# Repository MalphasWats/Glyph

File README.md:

# Glyph

![Glyph][GLYPH]

Glyph is a handheld gaming device based on the ATMega1284P micro controller.

This repository contains the mechanical components - KiCAD PCB & laser cut case.

## Specification

* ATMega1284P @ 16MHz. 128kB Flash, 16kB SRAM
* 1.3" monochrome OLED display
* 8 soft buttons
* 2 channel sound via piezo speaker
* 2 programmable red LEDs

## PCB

[KiCAD symbol/footprint library][KiLIB]

## Code

A software library for controlling the hardware and building simple games is available here:

[glyphlib][GLYPHLIB]

## Games

* [Argon][ARGON]
* ... more soon

[GLYPH]: resources/glyph.jpeg
[GLYPHLIB]: https://github.com/MalphasWats/glyphlib
[ARGON]: https://github.com/MalphasWats/Argon
[KiLIB]: https://github.com/MalphasWats/KiCADLib

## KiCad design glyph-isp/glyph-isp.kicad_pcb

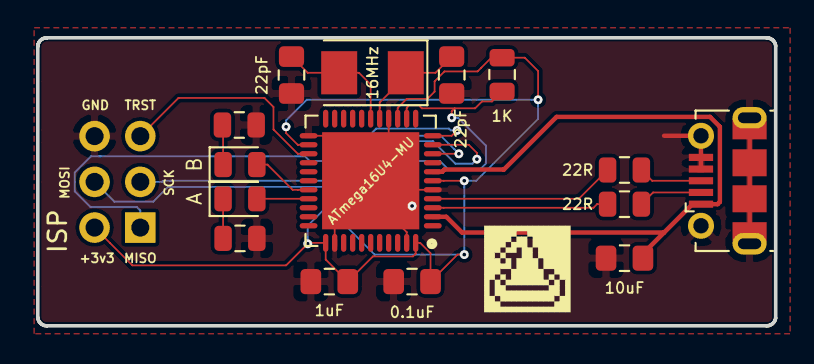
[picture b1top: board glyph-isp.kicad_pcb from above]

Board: 2 copper layers, 41.0 x 16.0 mm, 18 parts (1 on the bottom side), 18 nets.

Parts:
C0: 0.1uF; C_0805_2012Metric_Pad1.15x1.40mm_HandSolder
C1, C2: 22pF; C_0805_2012Metric_Pad1.15x1.40mm_HandSolder
C3: 1uF; C_0805_2012Metric_Pad1.15x1.40mm_HandSolder
C4: 10uF; C_0805_2012Metric_Pad1.15x1.40mm_HandSolder
D1: LED1; LED_0805_2012Metric
D2: LED2; LED_0805_2012Metric
HAT: HAT
J0, J1: ISP; PinHeader_2x03_P2.54mm_Vertical
J2: USB-Micro; USB_Micro-B_Molex-105017-0001
R1: 1K; R_0805_2012Metric
R2, R3: LED; R_0805_2012Metric
R4, R5: 22R; R_0805_2012Metric
U0: ATmega16U4-MU; QFN-44-1EP_7x7mm_P0.5mm_EP5.4x5.4mm
Y1: 16MHz; Crystal_SMD_5032-2Pin_5.0x3.2mm

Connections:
+3V3: C0.1, C3.1, J0.2, J1.2, R1.1, U0.6, U0.14, U0.24, U0.34, U0.44
D+: R4.1, U0.4
D-: R5.1, U0.3
GND: C0.2, C1.2, C2.2, C3.2, C4.1, J0.6, J1.6, J2.4, J2.5, J2.6, R2.2, R3.2, U0.5, U0.15, U0.23, U0.35, U0.43, U0.45
LED1: D1.2, U0.29
LED2: D2.2, U0.30
MISO: J0.1, J1.1, U0.11
MOSI: J0.4, J1.4, U0.10
unnamed: C1.1, U0.17, Y1.2
unnamed: C2.1, U0.16, Y1.1
unnamed: D1.1, R2.1
unnamed: D2.1, R3.1
unnamed: J2.2, R5.2
unnamed: J2.3, R4.2
RESET: J0.5, R1.2, U0.13
SCK: J0.3, J1.3, U0.9
TARGET_RESET: J1.5, U0.25
VBUS: C4.2, J2.1, U0.2, U0.7

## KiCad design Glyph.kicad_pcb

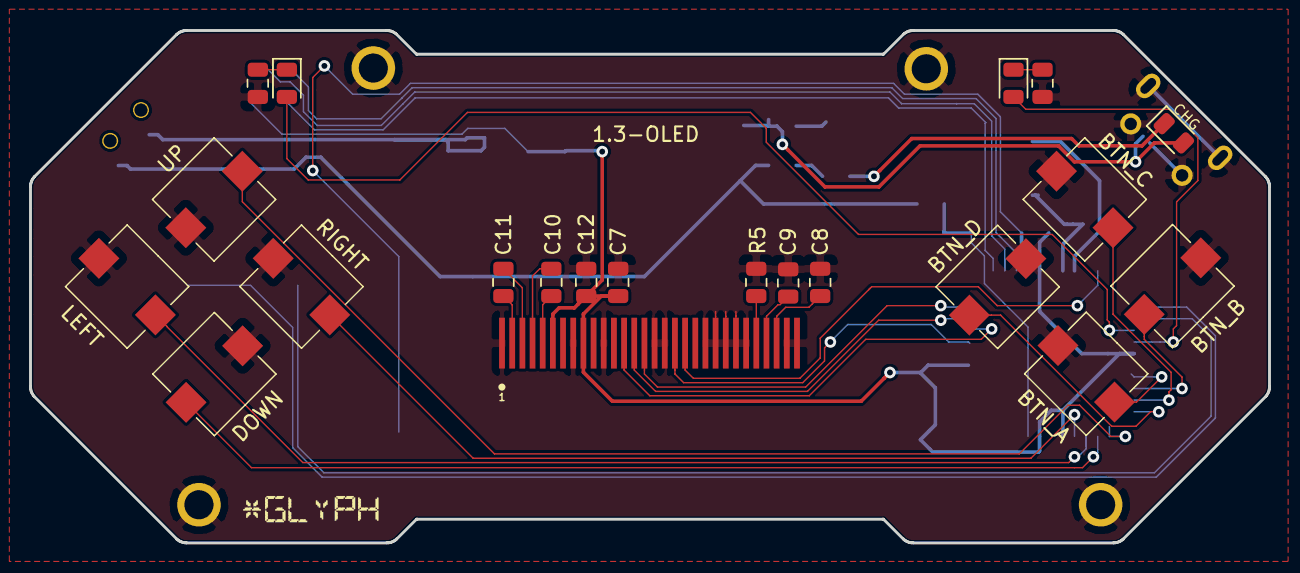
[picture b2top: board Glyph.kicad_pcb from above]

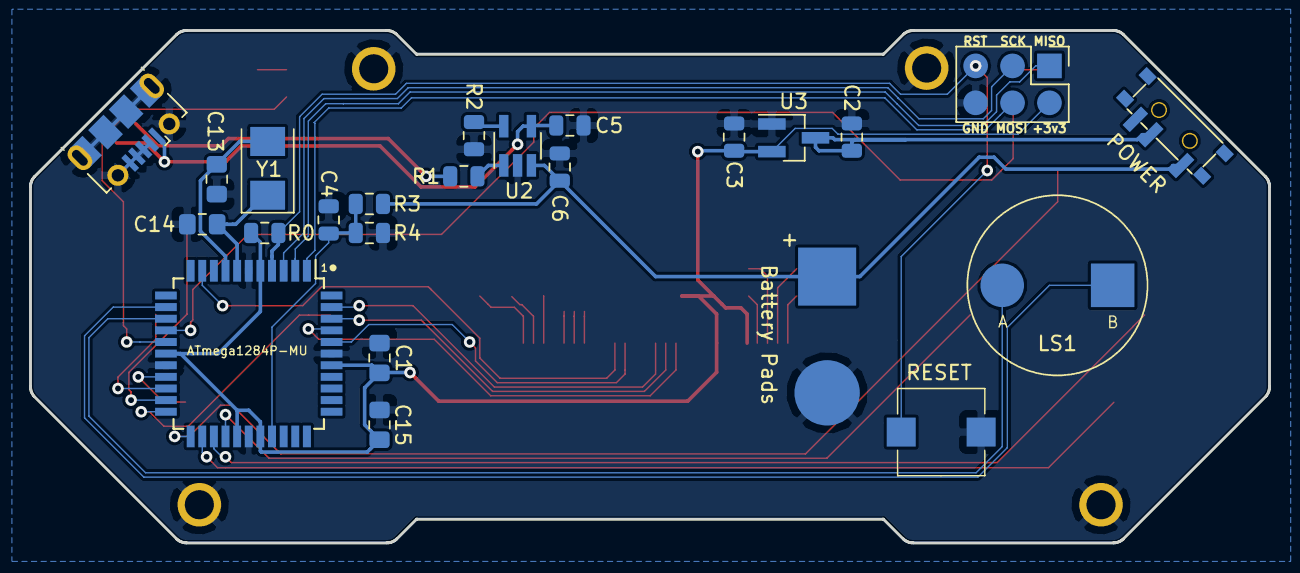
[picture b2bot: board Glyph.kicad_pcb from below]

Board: 2 copper layers, 85.3 x 35.3 mm, 50 parts (24 on the bottom side), 41 nets.

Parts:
C1, C15: 0.1uF; C_0805_2012Metric_Pad1.15x1.40mm_HandSolder
C2, C3, C4, C10, C11: 1uF; C_0805_2012Metric
C5, C6: 4.7uF; C_0805_2012Metric
C7, C12: 0.1uF; C_0805_2012Metric
C8: 47uF; C_0805_2012Metric
C9: 22uF; C_0805_2012Metric
C13, C14: 22pF; C_0805_2012Metric_Pad1.15x1.40mm_HandSolder
D0: CHG; LED_0805_2012Metric
D1: USR_1; LED_0805_2012Metric
D2: USR_2; LED_0805_2012Metric
J0: Battery Pads; 150mAh-Lipo
J1: ISP; ISP_SMD
J2: USB-Micro; USB_Micro-B_Molex-105017-0001
J3: Screw Point 1; M2_SCREW_HOLE
J4: Screw Point 2; M2_SCREW_HOLE
J5: Screw Point 3; M2_SCREW_HOLE
J6: Screw Point 4; M2_SCREW_HOLE
LOGO: LOGO
LS1: Speaker; Generic_Speaker
R0: 1K; R_0805_2012Metric
R1, R6, R7: LED; R_0805_2012Metric
R2: 2K; R_0805_2012Metric
R3, R4: 10M; R_0805_2012Metric
R5: 290k; R_0805_2012Metric
SW0: RESET; SW_SOFT_SMD_6mm
SW1: UP; SW_SOFT_SMD_6mm
SW2: DOWN; SW_SOFT_SMD_6mm
SW3: LEFT; SW_SOFT_SMD_6mm
SW4: RIGHT; SW_SOFT_SMD_6mm
SW5: BTN_A; SW_SOFT_SMD_6mm
SW6: BTN_B; SW_SOFT_SMD_6mm
SW7: BTN_C; SW_SOFT_SMD_6mm
SW8: BTN_D; SW_SOFT_SMD_6mm
SW9: POWER; ALPS-SSSS811101_SPDT
U0: ATmega1284P-MU; TQFP-44_10x10mm_P0.8mm
U1: 1.3-OLED; 1.3-OLED-bare-noslot
U2: CHG CTRL; SOT-23-5_HandSoldering
U3: Reg; SOT-23_Handsoldering
Y1: 20MHz; Crystal_SMD_5032-2Pin_5.0x3.2mm

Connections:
+3V3: C1.2, C3.1, C7.1, C12.1, C15.1, J1.2, R0.1, U0.5, U0.17, U0.27, U0.29, U0.38, U1.6, U1.9, U3.2
+BATT: C6.1, J0.1, R3.1, SW9.1, U2.3
BAT_MON: C4.1, R3.2, R4.1, U0.30
BTN_A: SW5.2, U0.19
BTN_B: SW6.2, U0.20
BTN_C: SW7.2, U0.21
BTN_D: SW8.2, U0.22
CHARGE: C5.1, D0.2, J2.1, U2.4
DOWN: SW2.2, U0.24
D_CS: U0.41, U1.13
D_DC: U0.43, U1.15
D_MOSI: U0.10, U1.19
D_RST: U0.42, U1.14
D_SCK: U0.40, U1.18
GND: C1.1, C2.2, C3.2, C4.2, C5.2, C6.2, C7.2, C8.2, C9.2, C12.2, C13.2, C14.2, C15.2, J0.2, J1.6, J2.2, J2.3, J2.4, J2.5, J2.6, J3.1, J4.1, J5.1, J6.1, R2.2, R4.2, R5.2, R6.2, R7.2, SW0.1, SW1.1, SW2.1, SW3.1, SW4.1, SW5.1, SW6.1, SW7.1, SW8.1, U0.6, U0.18, U0.28, U0.39, U1.1, U1.8, U1.11, U1.16, U1.17, U1.21, U1.22, U1.23, U1.24, U1.25, U1.29, U1.30, U2.2, U3.1
LEFT: SW3.2, U0.25
MISO: J1.1, U0.2
MOSI: J1.4, U0.1
unnamed: C2.1, SW9.2, U3.3
unnamed: C8.1, U1.28
unnamed: C9.1, U1.27
unnamed: C10.1, U1.4
unnamed: C10.2, U1.5
unnamed: C11.1, U1.2
unnamed: C11.2, U1.3
unnamed: C13.1, U0.8, Y1.2
unnamed: C14.1, U0.7, Y1.1
unnamed: D0.1, R1.2
unnamed: D1.1, R6.1
unnamed: D2.1, R7.1
unnamed: R1.1, U2.1
unnamed: R2.1, U2.5
unnamed: R5.1, U1.26
RESET: J1.5, R0.2, SW0.2, U0.4
RIGHT: SW4.2, U0.26
SCK: J1.3, U0.3
SNDA: LS1.2, U0.14
SNDB: LS1.1, U0.13
UP: SW1.2, U0.23
USR_LED_1: D1.2, U0.15
USR_LED_2: D2.2, U0.16

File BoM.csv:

"Id";"Designator";"Package";"Quantity";"Designation";"Supplier and ref";
1;"SW9";"ALPS-SSSS811101_SPDT";1;"POWER";;;
2;"J1";"ISP_SMD";1;"ISP";;;
3;"U1";"1.3-OLED-bare-noslot";1;"1.3-OLED";;;
4;"SW7";"SW_SOFT_SMD_6mm";1;"BTN_C";;;
5;"SW0";"SW_SOFT_SMD_6mm";1;"RESET";;;
6;"SW1";"SW_SOFT_SMD_6mm";1;"UP";;;
7;"SW2";"SW_SOFT_SMD_6mm";1;"DOWN";;;
8;"SW3";"SW_SOFT_SMD_6mm";1;"LEFT";;;
9;"SW4";"SW_SOFT_SMD_6mm";1;"RIGHT";;;
10;"SW5";"SW_SOFT_SMD_6mm";1;"BTN_A";;;
11;"SW6";"SW_SOFT_SMD_6mm";1;"BTN_B";;;
12;"J2";"USB_Micro-B_Molex-105017-0001";1;"USB-Micro";;;
13;"LS1";"Generic_Speaker";1;"Speaker";;;
14;"U2";"SOT-23-5_HandSoldering";1;"CHG CTRL";;;
15;"U3";"SOT-23_Handsoldering";1;"Reg";;;
16;"J3";"M2_SCREW_HOLE";1;"Screw Point 1";;;
17;"J4";"M2_SCREW_HOLE";1;"Screw Point 2";;;
18;"J5";"M2_SCREW_HOLE";1;"Screw Point 3";;;
19;"J6";"M2_SCREW_HOLE";1;"Screw Point 4";;;
20;"SW8";"SW_SOFT_SMD_6mm";1;"BTN_D";;;
21;"J0";"150mAh-Lipo";1;"Battery Pads";;;
22;"C2,C3,C4,C10,C11";"C_0805_2012Metric";5;"1uF";;;
23;"C5,C6";"C_0805_2012Metric";2;"4.7uF";;;
24;"C7,C12";"C_0805_2012Metric";2;"0.1uF";;;
25;"C8";"C_0805_2012Metric";1;"47uF";;;
26;"C9";"C_0805_2012Metric";1;"22uF";;;
27;"D1";"LED_0805_2012Metric";1;"USR_1";;;
28;"D2";"LED_0805_2012Metric";1;"USR_2";;;
29;"R0";"R_0805_2012Metric";1;"1K";;;
30;"R1,R6,R7";"R_0805_2012Metric";3;"LED";;;
31;"R2";"R_0805_2012Metric";1;"2K";;;
32;"R3,R4";"R_0805_2012Metric";2;"10M";;;
33;"R5";"R_0805_2012Metric";1;"290k";;;
34;"C1,C15";"C_0805_2012Metric_Pad1.15x1.40mm_HandSolder";2;"0.1uF";;;
35;"C13,C14";"C_0805_2012Metric_Pad1.15x1.40mm_HandSolder";2;"22pF";;;
36;"D0";"LED_0805_2012Metric";1;"CHG";;;
37;"U0";"TQFP-44_10x10mm_P0.8mm";1;"ATmega1284P-MU";;;
38;"Y1";"Crystal_SMD_5032-2Pin_5.0x3.2mm";1;"20MHz";;;

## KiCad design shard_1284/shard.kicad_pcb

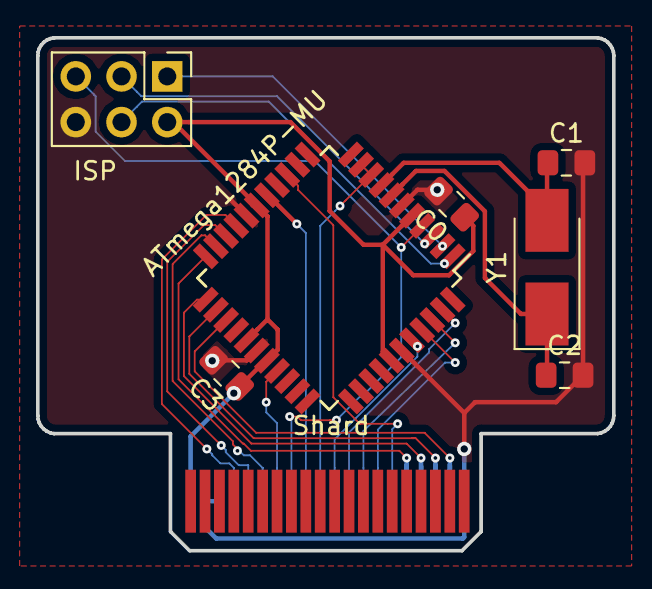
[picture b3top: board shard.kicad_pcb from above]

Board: 2 copper layers, 32.0 x 28.5 mm, 8 parts (0 on the bottom side), 23 nets.

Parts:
C0: 104; C_0805_2012Metric_Pad1.15x1.40mm_HandSolder
C1, C2, C3: 220; C_0805_2012Metric_Pad1.15x1.40mm_HandSolder
J0: Shard; Samtec_MEC8-120-02-L-D-RA1_Edge
J1: ISP; PinHeader_2x03_P2.54mm_Vertical
U1: ATmega1284P-MU; TQFP-44_10x10mm_P0.8mm
Y1: 16MHz; Crystal_SMD_5032-2Pin_5.0x3.2mm_HandSoldering

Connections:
+3V3: C0.1, C3.1, J0.2, J1.2, U1.5, U1.17, U1.27, U1.29, U1.38
BAT_MON: J0.14, U1.30
BTN_A: J0.8, U1.19
BTN_B: J0.10, U1.20
BTN_C: J0.12, U1.21
DOWN: J0.34, U1.23
D_CS: J0.28, U1.41
D_DC: J0.24, U1.43
D_MOSI: J0.20, U1.9, U1.10
D_RST: J0.26, U1.42
D_SCK: J0.22, U1.40
GND: C0.2, C1.2, C2.2, C3.2, J0.4, J0.6, J0.40, J1.6, U1.6, U1.18, U1.28, U1.39
LEFT: J0.36, U1.24
MISO: J1.1, U1.2
MOSI: J1.4, U1.1
unnamed: C1.1, U1.8, Y1.2
unnamed: C2.1, U1.7, Y1.1
RESET: J0.16, J1.5, U1.4
RIGHT: J0.38, U1.25
SCK: J1.3, U1.3
SND: J0.30, U1.14
UP: J0.32, U1.22
USR_LED: J0.18, U1.16

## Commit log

2019-02-01 Initial layout
2019-02-01 1.3-inch works better
2019-02-04 initial oled components
2019-02-05 added OLED circuit
2019-02-05 forgot to save it
2019-02-08 update layout
2019-02-08 new layout & traces
2019-02-10 tracks laid out
2019-02-10 1284 Shard initial design
2019-02-20 initial rework for no shard
2019-02-23 onboard isp
2019-02-24 retuned to fixed MCU
2019-02-24 moved a thing slightly
2019-02-26 USB-ISP Prototype
2019-02-26 Silkscreen
2019-03-05 capacitor label consistency
2019-03-05 capacitor values consistent
2019-03-05 added logo
2019-03-12 reworked ISP size
2019-03-22 cases
2019-03-22 pindiffs
2019-03-26 logo
2019-03-27 developing case
2019-04-12 3D case initial prototype
2019-04-15 tweak tolerance
2019-04-15 fix perimeter
2019-04-15 add speaker holes
2019-04-15 embiggened top to fit 3dp bottom
2019-04-15 3dp top
2019-04-15 3dp top tweak tolerances
2019-04-17 Added programming hole
2019-04-21 changed crystal to 16MHz
2019-04-22 update image
2019-11-23 case tweaks
